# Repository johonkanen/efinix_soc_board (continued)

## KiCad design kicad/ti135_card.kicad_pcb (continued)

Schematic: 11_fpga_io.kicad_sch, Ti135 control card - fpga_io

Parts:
U501: Ti135N484I3; LFBGA-484_18x18mm_Layout22x22_P0.8mm

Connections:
/adasel0_iso: U501.K19 (GPIOT_N_35); also elsewhere on the board
/adasel1_iso: U501.K18 (GPIOT_N_34); also elsewhere on the board
/adasel2_iso: U501.J19 (GPIOT_P_35); also elsewhere on the board
/adbsel0: U501.T19 (GPIOT_P_22_CLK16_P); also elsewhere on the board
/adbsel1: U501.T20 (GPIOT_P_21); also elsewhere on the board
/adbsel2: U501.R19 (GPIOT_N_21); also elsewhere on the board
/adc_cs_n: U501.N1 (GPIOB_P_04_EXTFB); also elsewhere on the board
/adc_sclk: U501.U20 (GPIOT_P_24_CLK18_P); also elsewhere on the board
/adc_sdo: U501.K17 (GPIOT_N_39_CLK15_N); also elsewhere on the board
/adclk_dab: U501.P19 (GPIOT_P_18); also elsewhere on the board
/adclk_iso: U501.J17 (GPIOT_P_34_PLLIN0); also elsewhere on the board
/clk1_iso: U501.L19 (GPIOT_P_37_CDI23_PLLIN0); also elsewhere on the board
/cs1_iso: U501.L17 (GPIOT_N_20); also elsewhere on the board
/dab_pwm_hi_sec: U501.M17 (GPIOT_P_20_PLLIN0); also elsewhere on the board
/dab_pwm_lo_sec: U501.P21 (GPIOT_N_17); also elsewhere on the board
/dab_pwm_pri_hi_iso: U501.N17 (GPIOT_P_02); also elsewhere on the board
/dab_pwm_pri_lo_iso: U501.P20 (GPIOT_P_17); also elsewhere on the board
/emmc_clk: U501.K4 (GPIOB_P_20_EXTSPICLK_CLK6_P); also elsewhere on the board
/emmc_cmd: U501.H2 (GPIOB_N_18_CLK5_N); also elsewhere on the board
/emmc_dat0: U501.F1 (GPIOB_N_22); also elsewhere on the board
/emmc_dat1: U501.F2 (GPIOB_N_24_CDI4); also elsewhere on the board
/emmc_dat2: U501.F3 (GPIOB_P_24_CDI5_EXTFB); also elsewhere on the board
/emmc_dat3: U501.E1 (GPIOB_P_22_EXTFB); also elsewhere on the board
/emmc_dat4: U501.E2 (GPIOB_P_23_CDI7_PLLIN0); also elsewhere on the board
/emmc_dat5: U501.D2 (GPIOB_N_23_CDI6); also elsewhere on the board
/emmc_dat6: U501.B1 (GPIOB_N_21_CLK7_N); also elsewhere on the board
/emmc_dat7: U501.G2 (GPIOB_P_18_CLK5_P); also elsewhere on the board
/emmc_ds: U501.B2 (GPIOB_P_21_CLK7_P); also elsewhere on the board
/emmc_rst_n: U501.A3 (GPIOB_P_28_CSO_CLK11_P); also elsewhere on the board
/eth_int_n: U501.M5 (GPIOB_N_09); also elsewhere on the board
/eth_mdc: U501.M2 (GPIOB_N_06_CDI18); also elsewhere on the board
/eth_mdio: U501.K3 (GPIOB_N_08); also elsewhere on the board
/eth_rst_n: U501.K2 (GPIOB_P_08); also elsewhere on the board
/flash_cs_n: U501.C1 (GPIOB_N_25_SSL_N); also elsewhere on the board
/flash_io0: U501.J4 (GPIOB_N_27_CDI0_CLK10_N); also elsewhere on the board
/flash_io1: U501.J5 (GPIOB_P_27_CDI1_CLK10_P); also elsewhere on the board
/flash_io2: U501.G3 (GPIOB_N_26_CDI2); also elsewhere on the board
/flash_io3: U501.C2 (GPIOB_P_25_CDI3_PLLIN0); also elsewhere on the board
/flash_sck: U501.G4 (GPIOB_P_26_CCK); also elsewhere on the board
/fpga_cbsel0: U501.J1 (GPIOB_N_19_CBSEL0); also elsewhere on the board
/fpga_cbsel1: U501.H1 (GPIOB_P_19_CBSEL1); also elsewhere on the board
/fpga_csi: U501.A2 (GPIOB_N_28_CSI_CLK11_N); also elsewhere on the board
/fpga_ssu_n: U501.L4 (GPIOB_N_20_SSU_N_CLK6_N); also elsewhere on the board
/fpga_test_n: U501.L7 (GPIOB_N_17_TEST_N_CLK4_N); also elsewhere on the board
/gpio_bypass_rly_iso: U501.T21 (GPIOT_N_24_CLK18_N); also elsewhere on the board
/gpio_bypass_rly_isolated: U501.K16 (GPIOT_P_39_CLK15_P); also elsewhere on the board
/inu_adclk: U501.R21 (GPIOT_P_25_CLK19_P); also elsewhere on the board
/j3_oe_n: U501.L5 (GPIOB_P_09); also elsewhere on the board
/lcd_cs_n: U501.L22 (GPIOR_84); also elsewhere on the board
/lcd_dc: U501.H9 (GPIOL_32_PLLIN1); also elsewhere on the board
/lcd_led: U501.H7 (GPIOL_31); also elsewhere on the board
/lcd_miso: U501.H6 (GPIOL_27_CLK25); also elsewhere on the board
/lcd_mosi: U501.L8 (GPIOR_130_PLLIN1); also elsewhere on the board
/lcd_reset_n: U501.L21 (GPIOR_83); also elsewhere on the board
/lcd_sck: U501.H8 (GPIOL_33); also elsewhere on the board
/led0_n: U501.M22 (GPIOR_82)
/led1_n: U501.M8 (GPIOR_127_CLK8)
/mdata_dab: U501.N20 (GPIOR_79); also elsewhere on the board
/mdata_inu: U501.M20 (GPIOR_78_PLLIN1); also elsewhere on the board
/mdata_iso: U501.N21 (GPIOR_80_CLK12); also elsewhere on the board
/pwm_g1_iso: U501.P18 (GPIOT_N_04_CLK31_N); also elsewhere on the board
/pwm_g2_iso: U501.R18 (GPIOT_N_22_CLK16_N); also elsewhere on the board
/pwm_g3_iso: U501.N16 (GPIOT_N_02); also elsewhere on the board
/pwm_g4_iso: U501.M18 (GPIOT_P_19_EXTFB); also elsewhere on the board
/pwm_q5: U501.T16 (GPIOT_P_00_CLK26_P); also elsewhere on the board
/pwm_q6: U501.R22 (GPIOT_N_25_CLK19_N); also elsewhere on the board
/pwm_q7: U501.T17 (GPIOT_P_01_CLK27_P); also elsewhere on the board
/pwm_q8: U501.T22 (GPIOT_N_23_CLK17_N); also elsewhere on the board
/pwm_trans1_iso: U501.M19 (GPIOT_N_19); also elsewhere on the board
/pwm_trans2_iso: U501.L20 (GPIOT_N_37_CDI22); also elsewhere on the board
/pwm_trans3_iso: U501.N18 (GPIOT_N_18); also elsewhere on the board
/pwm_trans4: U501.R17 (GPIOT_P_04_CLK31_P); also elsewhere on the board
/pwm_trans5: U501.U22 (GPIOT_P_23_CLK17_P); also elsewhere on the board
/pwm_trans6: U501.R16 (GPIOT_N_01_CLK27_N); also elsewhere on the board
/refclk_bl0: U501.N7 (GPIOB_P_00_PLLIN0); also elsewhere on the board
/refclk_bl1: U501.R3 (GPIOB_P_03_PLLIN0); also elsewhere on the board
/refclk_bl2: U501.L2 (GPIOB_P_06_CDI19_PLLIN0); also elsewhere on the board
/rgmii_rx_ctl: U501.N2 (GPIOB_N_12_CDI12); also elsewhere on the board
/rgmii_rxc: U501.P5 (GPIOB_P_14_CLK1_P); also elsewhere on the board
/rgmii_rxd0: U501.N3 (GPIOB_P_12_CDI13); also elsewhere on the board
/rgmii_rxd1: U501.R4 (GPIOB_N_14_CLK1_N); also elsewhere on the board
/rgmii_rxd2: U501.N5 (GPIOB_N_11_CDI14); also elsewhere on the board
/rgmii_rxd3: U501.N6 (GPIOB_P_11_CDI15); also elsewhere on the board
/rgmii_tx_ctl: U501.R2 (GPIOB_N_03); also elsewhere on the board
/rgmii_txc: U501.P6 (GPIOB_N_00); also elsewhere on the board
/rgmii_txd0: U501.P1 (GPIOB_N_04); also elsewhere on the board
/rgmii_txd1: U501.P3 (GPIOB_N_05); also elsewhere on the board
/rgmii_txd2: U501.T6 (GPIOB_N_07_CDI16); also elsewhere on the board
/rgmii_txd3: U501.P4 (GPIOB_P_05); also elsewhere on the board
/sdata1_iso: U501.N22 (GPIOR_81_CLK13); also elsewhere on the board
/t_clk: U501.J6 (GPIOR_131_PERST_Q0_N); also elsewhere on the board
/t_cs_n: U501.F5 (GPIOL_34_PLLIN1); also elsewhere on the board
/t_din: U501.H5 (GPIOR_132); also elsewhere on the board
/t_do: U501.F4 (GPIOL_26_CLK24); also elsewhere on the board
/t_irq: U501.K6 (GPIOR_129_PLLIN1); also elsewhere on the board
/uart_rx: U501.K7 (GPIOR_128_CLK9); also elsewhere on the board
/uart_tx: U501.G6 (GPIOL_28); also elsewhere on the board

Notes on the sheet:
U501 Ti135N484I3 I/O banks. Signal <-> ball assignment from efinity/pinplan/pinplan.py (Interface Designer project, design check passed). Change pins there, then re-run this script. HSIO banks (4A, 4B, 2A-2C) are 1.8 V; HVIO banks (BR1_BL3, BR0, TR1) are 3.3 V.

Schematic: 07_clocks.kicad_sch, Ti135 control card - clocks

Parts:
C701: 100n; C_0201_0603Metric; LCSC C190183
R701, R702, R703: 33R; R_0402_1005Metric; LCSC C25105
Y701: OT322525MJBA4SL; Oscillator_SMD_SiT_PQFN-4Pin_3.2x2.5mm; LCSC C669088

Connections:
1V8: C701.1, Y701.1 (EN), Y701.4 (Vdd); also elsewhere on the board
/refclk_bl0: R701.2; also elsewhere on the board
/refclk_bl1: R702.2; also elsewhere on the board
/refclk_bl2: R703.2; also elsewhere on the board
GND: C701.2, Y701.2 (GND); also elsewhere on the board
unnamed: R701.1, R702.1, R703.1, Y701.3 (OUT)

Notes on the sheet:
25 MHz reference: Y701 -> 3 x 33 R (at Y701) -> PLL_BL0/BL1/BL2 reference pins N7/R3/L2 (bank 4B, 1.8 V). Star from the oscillator, one series resistor per branch; keep the branches short and similar in length.
Y701 EN (pin 1) tied to 1V8: always enabled.

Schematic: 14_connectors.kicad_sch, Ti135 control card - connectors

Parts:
J2: UART 3.3V; PinHeader_1x03_P2.54mm_Vertical; LCSC C2937625
J3: 2x19 1.27mm socket (bottom); PinSocket_2x19_P1.27mm_Vertical_Drill0.6; LCSC C27985219
J5: LCD 1x14 2.54mm; PinHeader_1x14_P2.54mm_Vertical; LCSC C22465874
R1401, R1402: 1k; R_0402_1005Metric; LCSC C11702
RN1401, RN1402, RN1403, RN1404, RN1405, RN1406, RN1407, RN1408: 4x10k; R_Array_Convex_4x0402; MPN 4D02WGJ0103TCE; LCSC C25725

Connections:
3V3: J5.14; also elsewhere on the board
/adasel0_iso_3v3: J3.11, RN1402.2 (R2.1); also elsewhere on the board
/adasel1_iso_3v3: J3.10, RN1402.1 (R1.1); also elsewhere on the board
/adasel2_iso_3v3: J3.9, RN1401.4 (R4.1); also elsewhere on the board
/adclk_dab_3v3: J3.24, RN1405.3 (R3.1); also elsewhere on the board
/adclk_iso_3v3: J3.7, RN1401.2 (R2.1); also elsewhere on the board
/clk1_iso_3v3: J3.14, RN1403.1 (R1.1); also elsewhere on the board
/cs1_iso_3v3: J3.13, RN1402.4 (R4.1); also elsewhere on the board
/dab_pwm_hi_sec_3v3: J3.27, RN1406.2 (R2.1); also elsewhere on the board
/dab_pwm_lo_sec_3v3: J3.29, RN1406.4 (R4.1); also elsewhere on the board
/dab_pwm_pri_hi_iso_3v3: J3.22, RN1405.1 (R1.1); also elsewhere on the board
/dab_pwm_pri_lo_iso_3v3: J3.23, RN1405.2 (R2.1); also elsewhere on the board
/gpio_bypass_rly_iso_3v3: J3.36, RN1408.3 (R3.1); also elsewhere on the board
/gpio_bypass_rly_isolated_3v3: J3.8, RN1401.3 (R3.1); also elsewhere on the board
/inu_adclk_3v3: J3.32, RN1407.3 (R3.1); also elsewhere on the board
/isoada1: J3.4; also elsewhere on the board
/isoada2: J3.3; also elsewhere on the board
/isoada3: J3.1; also elsewhere on the board
/lcd_cs_n: J5.12; also elsewhere on the board
/lcd_dc: J5.10; also elsewhere on the board
/lcd_led: J5.7; also elsewhere on the board
/lcd_miso: J5.6; also elsewhere on the board
/lcd_mosi: J5.9; also elsewhere on the board
/lcd_reset_n: J5.11; also elsewhere on the board
/lcd_sck: J5.8; also elsewhere on the board
/mdata_dab: J3.26, RN1406.1 (R1.1); also elsewhere on the board
/mdata_inu: J3.34, RN1408.1 (R1.1); also elsewhere on the board
/mdata_iso: J3.6, RN1401.1 (R1.1); also elsewhere on the board
/pwm_g1_iso_3v3: J3.20, RN1404.3 (R3.1); also elsewhere on the board
/pwm_g2_iso_3v3: J3.19, RN1404.2 (R2.1); also elsewhere on the board
/pwm_g3_iso_3v3: J3.21, RN1404.4 (R4.1); also elsewhere on the board
/pwm_g4_iso_3v3: J3.18, RN1404.1 (R1.1); also elsewhere on the board
/pwm_q5_3v3: J3.30, RN1407.1 (R1.1); also elsewhere on the board
/pwm_q6_3v3: J3.31, RN1407.2 (R2.1); also elsewhere on the board
/pwm_q7_3v3: J3.37, RN1408.4 (R4.1); also elsewhere on the board
/pwm_q8_3v3: J3.33, RN1407.4 (R4.1); also elsewhere on the board
/pwm_trans1_iso_3v3: J3.15, RN1403.2 (R2.1); also elsewhere on the board
/pwm_trans2_iso_3v3: J3.16, RN1403.3 (R3.1); also elsewhere on the board
/pwm_trans3_iso_3v3: J3.17, RN1403.4 (R4.1); also elsewhere on the board
/pwm_trans4_3v3: J3.25, RN1405.4 (R4.1); also elsewhere on the board
/pwm_trans5_3v3: J3.35, RN1408.2 (R2.1); also elsewhere on the board
/pwm_trans6_3v3: J3.28, RN1406.3 (R3.1); also elsewhere on the board
/res1: J3.38; also elsewhere on the board
/sdata1_iso: J3.12, RN1402.3 (R3.1); also elsewhere on the board
/t_clk: J5.5; also elsewhere on the board
/t_cs_n: J5.4; also elsewhere on the board
/t_din: J5.3; also elsewhere on the board
/t_do: J5.2; also elsewhere on the board
/t_irq: J5.1; also elsewhere on the board
/uart_rx: R1401.1; also elsewhere on the board
/uart_tx: R1402.1; also elsewhere on the board
GND: J2.3, J3.2, J3.5, J5.13, RN1401.5 (R4.2), RN1401.6 (R3.2), RN1401.7 (R2.2), RN1401.8 (R1.2), RN1402.5 (R4.2), RN1402.6 (R3.2), RN1402.7 (R2.2), RN1402.8 (R1.2), RN1403.5 (R4.2), RN1403.6 (R3.2), RN1403.7 (R2.2), RN1403.8 (R1.2), RN1404.5 (R4.2), RN1404.6 (R3.2), RN1404.7 (R2.2), RN1404.8 (R1.2), RN1405.5 (R4.2), RN1405.6 (R3.2), RN1405.7 (R2.2), RN1405.8 (R1.2), RN1406.5 (R4.2), RN1406.6 (R3.2), RN1406.7 (R2.2), RN1406.8 (R1.2), RN1407.5 (R4.2), RN1407.6 (R3.2), RN1407.7 (R2.2), RN1407.8 (R1.2), RN1408.5 (R4.2), RN1408.6 (R3.2), RN1408.7 (R2.2), RN1408.8 (R1.2); also elsewhere on the board
unnamed: J2.1, R1401.2
unnamed: J2.2, R1402.2

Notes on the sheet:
J5: LCD/touch header, Ti60 J4 pinout (wired to the LCD with jumper wires).
J3 = baseboard J11 (2x19 1.27 mm socket on B.Cu, pin n = baseboard pin n, see MECHANICAL.md). Every signal pin has a 10 k pull-down so the power board sees low while the FPGA is unconfigured and the translators are disabled (MIGRATION_PLAN.md 3.2).
J2: FPGA UART, Ti60 J8 pinout.
lcd_mosi / lcd_miso exchanged at J5 2026-11-17

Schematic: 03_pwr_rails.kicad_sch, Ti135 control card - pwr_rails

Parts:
C301, C311, C331, C341: 10u; C_0603_1608Metric; LCSC C109457
C302, C312, C332, C342: 22u; C_0603_1608Metric; LCSC C109447
C303, C313, C335, C343: 100n; C_0201_0603Metric; LCSC C190183
C304, C314, C333, C344: 47u; C_0805_2012Metric; LCSC C16780
C305, C315, C334, C345: 33p; C_0201_0603Metric; LCSC C277477
L301, L311, L331, L341: 1u; L_2520_FTC252012S; MPN FTC252012S1R0MBCA; LCSC C5832370
R301, R311, R331, R341: 200k; R_0201_0603Metric; LCSC C138163
R302: 100k; R_0201_0603Metric; LCSC C106224
R312: 44.2k; R_0201_0603Metric; LCSC C226551
R332: 475k; R_0201_0603Metric; LCSC C388079
R342: 243k; R_0201_0603Metric; LCSC C423644
U301, U311: AP61202Z6-7; SOT-563; LCSC C5188956
U331, U341: AP61203Z6-7; SOT-563; LCSC C5244557

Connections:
0V85: C332.1, C333.1, C334.1, L331.2, R331.1; also elsewhere on the board
1V1: C342.1, C344.1, C345.1, L341.2, R341.1; also elsewhere on the board
1V8: C302.1, C304.1, C305.1, L301.2, R301.1; also elsewhere on the board
3V3: C312.1, C314.1, C315.1, L311.2, R311.1; also elsewhere on the board
5V0: C301.1, C303.1, C311.1, C313.1, C331.1, C335.1, C341.1, C343.1, U301.3 (VIN), U301.5 (EN), U311.3 (VIN), U311.5 (EN), U331.3 (VIN), U341.3 (VIN); also elsewhere on the board
/pg_group1: U301.6 (PG), U311.6 (PG), U331.5 (EN), U341.5 (EN); also elsewhere on the board
GND: C301.2, C302.2, C303.2, C304.2, C311.2, C312.2, C313.2, C314.2, C331.2, C332.2, C333.2, C335.2, C341.2, C342.2, C343.2, C344.2, R302.2, R312.2, R332.2, R342.2, U301.2 (GND), U311.2 (GND), U331.2 (GND), U341.2 (GND); also elsewhere on the board
unnamed: C305.2, R301.2, R302.1, U301.1 (FB)
unnamed: L301.1, U301.4 (SW)
unnamed: C315.2, R311.2, R312.1, U311.1 (FB)
unnamed: L311.1, U311.4 (SW)
unnamed: C334.2, R331.2, R332.1, U331.1 (FB)
unnamed: L331.1, U331.4 (SW)
unnamed: C345.2, R341.2, R342.1, U341.1 (FB)
unnamed: L341.1, U341.4 (SW)

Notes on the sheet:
1V1 DDR I/O + LPDDR4 VDD2/VDDQ (group 2)
1V8 (group 1)
0V85 DDR PHY (group 2)
3V3 (group 1)
Group 1: 1V8 (VCCAUX, HSIO, LPDDR4 VDD1, eMMC VCCQ, flash), 3V3 (HVIO, eMMC VCC, PHY, translators). Group 2 (EN = pg_group1): 0V85 (DDR PHY VDD_PHY / VDDPLL), 1V1 (DDR VDDQ/VDDQX/VDDQ_CK, LPDDR4 VDD2/VDDQ).

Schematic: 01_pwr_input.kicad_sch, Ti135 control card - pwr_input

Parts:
C101: 47u; C_1206_3216Metric; LCSC C96123
C102: 22u; C_0805_2012Metric; LCSC C45783
C103: 100n; C_0402_1005Metric; LCSC C1525
C104, C105: 1u; C_0402_1005Metric; LCSC C52923
J6: 2x3 1.27mm (bottom); PinSocket_2x03_P1.27mm_Vertical; LCSC C22373841
J101: 5V0 bench input; PinHeader_1x02_P2.54mm_Vertical; LCSC C492401
U101: NCP163ASN330T1G; SOT-23-5; LCSC C603656

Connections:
3V3_analog: C105.1, U101.5 (VOUT); also elsewhere on the board
5V0: C101.1, C102.1, C103.1, C104.1, J6.2, J6.4, J6.6, J101.1, U101.1 (VIN), U101.3 (EN); also elsewhere on the board
GND: C101.2, C102.2, C103.2, C104.2, C105.2, J6.1, J6.3, J6.5, J101.2, U101.2 (GND); also elsewhere on the board

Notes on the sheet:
J101: 2.54 mm 1x2 header near J6 to power the card from a bench supply with female jumpers, without the baseboard (pin 1 = 5V0, pin 2 = GND). Do not feed it while the baseboard powers J6.
3V3_analog: LDO for the ADC block (sheet 13).
J6 = baseboard J12 (2x3 1.27 mm on B.Cu, MECHANICAL.md): 5V0 = baseboard 5V_ISOL, GND = ISOGND. Supply budget and limits: POWER_BUDGET.md (baseboard U8 to be upgraded to 1.5-2 A).
Input bulk (the regulators also have their own 10u).

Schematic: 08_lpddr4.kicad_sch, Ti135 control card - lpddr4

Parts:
C803: 22u; C_0402_1005Metric; LCSC C415703
C804, C805, C810, C811, C812, C813, C814, C815, C816, C817, C818, C819, C820, C821, C822, C827, C828, C829, C830, C831, C832, C833, C834, C835, C836, C837, C838, C839, C840: 100n; C_0201_0603Metric; LCSC C190183
C806, C807, C823, C824: 22u; C_0402_1005Metric; LCSC C415703; not fitted
C808, C809, C825, C826: 1u; C_0201_0603Metric; LCSC C272877
R801: 240R 0.5%; R_0201_0603Metric; MPN RC0201DR-07240RL; LCSC C851687
R802: 240R 1%; R_0402_1005Metric; LCSC C25094
R803: 15R; R_0402_1005Metric; LCSC C25083
R804: 10k 1%; R_0201_0603Metric; LCSC C106225
U501: Ti135N484I3; LFBGA-484_18x18mm_Layout22x22_P0.8mm
U801: H9HCNNN8KUMLHR-NMO; BGA-200_10x15mm_Layout12x22_P0.8x0.65mm; LCSC C51891855

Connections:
1V1: C806.1, C807.1, C808.1, C809.1, C810.1, C811.1, C812.1, C813.1, C814.1, C815.1, C816.1, C817.1, C818.1, C819.1, C820.1, C821.1, C822.1, C823.1, C824.1, C825.1, C826.1, C827.1, C828.1, C829.1, C830.1, C831.1, C832.1, C833.1, C834.1, C835.1, C836.1, C837.1, C838.1, C839.1, C840.1, R802.2, U801.A4 (VDD2), U801.A9 (VDD2), U801.AA3 (VDDQ), U801.AA5 (VDDQ), U801.AA8 (VDDQ), U801.AA10 (VDDQ), U801.AB4 (VDD2), U801.AB9 (VDD2), U801.B3 (VDDQ), U801.B5 (VDDQ), U801.B8 (VDDQ), U801.B10 (VDDQ), U801.D1 (VDDQ), U801.D5 (VDDQ), U801.D8 (VDDQ), U801.D12 (VDDQ), U801.F3 (VDDQ), U801.F5 (VDD2), U801.F8 (VDD2), U801.F10 (VDDQ), U801.G2 (ODT_CA_A), U801.H1 (VDD2), U801.H5 (VDD2), U801.H8 (VDD2), U801.H12 (VDD2), U801.K1 (VDD2), U801.K3 (VDD2), U801.K10 (VDD2), U801.K12 (VDD2), U801.N1 (VDD2), U801.N3 (VDD2), U801.N10 (VDD2), U801.N12 (VDD2), U801.R1 (VDD2), U801.R5 (VDD2), U801.R8 (VDD2), U801.R12 (VDD2), U801.T2 (ODT_CA_B), U801.U3 (VDDQ), U801.U5 (VDD2), U801.U8 (VDD2), U801.U10 (VDDQ), U801.W1 (VDDQ), U801.W5 (VDDQ), U801.W8 (VDDQ), U801.W12 (VDDQ); also elsewhere on the board
1V8: C803.1, C804.1, C805.1, U801.F1 (VDD1), U801.F12 (VDD1), U801.G4 (VDD1), U801.G9 (VDD1), U801.T4 (VDD1), U801.T9 (VDD1), U801.U1 (VDD1), U801.U12 (VDD1); also elsewhere on the board
/08 lpddr4/ddr_ca0: U501.AB15 (DDR_A[0]), U801.H2 (CA0_A), U801.R2 (CA0_B)
/08 lpddr4/ddr_ca1: U501.AA15 (DDR_A[1]), U801.J2 (CA1_A), U801.P2 (CA1_B)
/08 lpddr4/ddr_ca2: U501.AA14 (DDR_A[2]), U801.H9 (CA2_A), U801.R9 (CA2_B)
/08 lpddr4/ddr_ca3: U501.Y14 (DDR_A[3]), U801.H10 (CA3_A), U801.R10 (CA3_B)
/08 lpddr4/ddr_ca4: U501.W14 (DDR_A[4]), U801.H11 (CA4_A), U801.R11 (CA4_B)
/08 lpddr4/ddr_ca5: U501.W13 (DDR_A[5]), U801.J11 (CA5_A), U801.P11 (CA5_B)
/08 lpddr4/ddr_ck_N: U501.AA13 (DDR_CK_N), U801.J9 (CK_C_A), U801.P9 (CK_C_B)
/08 lpddr4/ddr_ck_P: U501.AB13 (DDR_CK), U801.J8 (CK_T_A), U801.P8 (CK_T_B)
/08 lpddr4/ddr_cke0: R803.2, U801.J4 (CKE0_A), U801.P4 (CKE0_B)
/08 lpddr4/ddr_cke0_fpga: R803.1, U501.AB11 (DDR_CKE[0])
/08 lpddr4/ddr_cs0_n: U501.AB9 (DDR_CS_N[0]), U801.H4 (CS0_A)
/08 lpddr4/ddr_cs2_n: U501.AA8 (DDR_CS_N[2]), U801.R4 (CS0_B)
/08 lpddr4/ddr_dm0: U501.W3 (DDR_DM[0]), U801.C3 (DMI0_A)
/08 lpddr4/ddr_dm1: U501.AA3 (DDR_DM[1]), U801.C10 (DMI1_A)
/08 lpddr4/ddr_dm2: U501.W18 (DDR_DM[2]), U801.Y3 (DMI0_B)
/08 lpddr4/ddr_dm3: U501.Y20 (DDR_DM[3]), U801.Y10 (DMI1_B)
/08 lpddr4/ddr_dq0: U501.U2 (DDR_DQ[1]), U801.B2 (DQ0_A)
/08 lpddr4/ddr_dq1: U501.AB2 (DDR_DQ[6]), U801.C2 (DQ1_A)
/08 lpddr4/ddr_dq2: U501.V3 (DDR_DQ[3]), U801.E2 (DQ2_A)
/08 lpddr4/ddr_dq3: U501.U3 (DDR_DQ[0]), U801.F2 (DQ3_A)
/08 lpddr4/ddr_dq4: U501.Y2 (DDR_DQ[4]), U801.F4 (DQ4_A)
/08 lpddr4/ddr_dq5: U501.AA2 (DDR_DQ[7]), U801.E4 (DQ5_A)
/08 lpddr4/ddr_dq6: U501.AA1 (DDR_DQ[5]), U801.C4 (DQ6_A)
/08 lpddr4/ddr_dq7: U501.U1 (DDR_DQ[2]), U801.B4 (DQ7_A)
/08 lpddr4/ddr_dq8: U501.W4 (DDR_DQ[11]), U801.B11 (DQ8_A)
/08 lpddr4/ddr_dq9: U501.V5 (DDR_DQ[9]), U801.C11 (DQ9_A)
/08 lpddr4/ddr_dq10: U501.AB5 (DDR_DQ[13]), U801.E11 (DQ10_A)
/08 lpddr4/ddr_dq11: U501.AA6 (DDR_DQ[14]), U801.F11 (DQ11_A)
/08 lpddr4/ddr_dq12: U501.AB7 (DDR_DQ[15]), U801.F9 (DQ12_A)
/08 lpddr4/ddr_dq13: U501.W5 (DDR_DQ[10]), U801.E9 (DQ13_A)
/08 lpddr4/ddr_dq14: U501.AA5 (DDR_DQ[12]), U801.C9 (DQ14_A)
/08 lpddr4/ddr_dq15: U501.U4 (DDR_DQ[8]), U801.B9 (DQ15_A)
/08 lpddr4/ddr_dq16: U501.V18 (DDR_DQ[20]), U801.AA2 (DQ0_B)
/08 lpddr4/ddr_dq17: U501.AB17 (DDR_DQ[19]), U801.Y2 (DQ1_B)
/08 lpddr4/ddr_dq18: U501.Y16 (DDR_DQ[17]), U801.V2 (DQ2_B)
/08 lpddr4/ddr_dq19: U501.W16 (DDR_DQ[23]), U801.U2 (DQ3_B)
/08 lpddr4/ddr_dq20: U501.AA16 (DDR_DQ[16]), U801.U4 (DQ4_B)
/08 lpddr4/ddr_dq21: U501.V16 (DDR_DQ[22]), U801.V4 (DQ5_B)
/08 lpddr4/ddr_dq22: U501.AA17 (DDR_DQ[18]), U801.Y4 (DQ6_B)
/08 lpddr4/ddr_dq23: U501.V17 (DDR_DQ[21]), U801.AA4 (DQ7_B)
/08 lpddr4/ddr_dq24: U501.W21 (DDR_DQ[29]), U801.AA11 (DQ8_B)
/08 lpddr4/ddr_dq25: U501.AA20 (DDR_DQ[26]), U801.Y11 (DQ9_B)
/08 lpddr4/ddr_dq26: U501.AA19 (DDR_DQ[27]), U801.V11 (DQ10_B)
/08 lpddr4/ddr_dq27: U501.W19 (DDR_DQ[30]), U801.U11 (DQ11_B)
/08 lpddr4/ddr_dq28: U501.W20 (DDR_DQ[31]), U801.U9 (DQ12_B)
/08 lpddr4/ddr_dq29: U501.AB19 (DDR_DQ[24]), U801.V9 (DQ13_B)
/08 lpddr4/ddr_dq30: U501.AB21 (DDR_DQ[25]), U801.Y9 (DQ14_B)
/08 lpddr4/ddr_dq31: U501.W22 (DDR_DQ[28]), U801.AA9 (DQ15_B)
/08 lpddr4/ddr_dqs0_N: U501.W1 (DDR_DQS_N[0]), U801.E3 (DQS0_C_A)
/08 lpddr4/ddr_dqs0_P: U501.W2 (DDR_DQS[0]), U801.D3 (DQS0_T_A)
/08 lpddr4/ddr_dqs1_N: U501.AA4 (DDR_DQS_N[1]), U801.E10 (DQS1_C_A)
/08 lpddr4/ddr_dqs1_P: U501.Y4 (DDR_DQS[1]), U801.D10 (DQS1_T_A)
/08 lpddr4/ddr_dqs2_N: U501.AA18 (DDR_DQS_N[2]), U801.V3 (DQS0_C_B)
/08 lpddr4/ddr_dqs2_P: U501.Y18 (DDR_DQS[2]), U801.W3 (DQS0_T_B)
/08 lpddr4/ddr_dqs3_N: U501.AA22 (DDR_DQS_N[3]), U801.V10 (DQS1_C_B)
/08 lpddr4/ddr_dqs3_P: U501.AA21 (DDR_DQS[3]), U801.W10 (DQS1_T_B)
/08 lpddr4/ddr_rst_n: R804.1, U501.AA12 (DDR_RST_N), U801.T11 (RESET_N)
GND: C803.2, C804.2, C805.2, C806.2, C807.2, C808.2, C809.2, C810.2, C811.2, C812.2, C813.2, C814.2, C815.2, C816.2, C817.2, C818.2, C819.2, C820.2, C821.2, C822.2, C823.2, C824.2, C825.2, C826.2, C827.2, C828.2, C829.2, C830.2, C831.2, C832.2, C833.2, C834.2, C835.2, C836.2, C837.2, C838.2, C839.2, C840.2, R801.2, R804.2, U801.A3 (VSS), U801.A10 (VSS), U801.AB3 (VSS), U801.AB5 (VSS), U801.AB8 (VSS), U801.AB10 (VSS), U801.C1 (VSS), U801.C5 (VSS), U801.C8 (VSS), U801.C12 (VSS), U801.D2 (VSS), U801.D4 (VSS), U801.D9 (VSS), U801.D11 (VSS), U801.E1 (VSS), U801.E5 (VSS), U801.E8 (VSS), U801.E12 (VSS), U801.G1 (VSS), U801.G3 (VSS), U801.G5 (VSS), U801.G8 (VSS), U801.G10 (VSS), U801.G12 (VSS), U801.J1 (VSS), U801.J3 (VSS), U801.J10 (VSS), U801.J12 (VSS), U801.K2 (VSS), U801.K4 (VSS), U801.K9 (VSS), U801.K11 (VSS), U801.N2 (VSS), U801.N4 (VSS), U801.N9 (VSS), U801.N11 (VSS), U801.P1 (VSS), U801.P3 (VSS), U801.P10 (VSS), U801.P12 (VSS), U801.T1 (VSS), U801.T3 (VSS), U801.T5 (VSS), U801.T8 (VSS), U801.T10 (VSS), U801.T12 (VSS), U801.V1 (VSS), U801.V5 (VSS), U801.V8 (VSS), U801.V12 (VSS), U801.W2 (VSS), U801.W4 (VSS), U801.W9 (VSS), U801.W11 (VSS), U801.Y1 (VSS), U801.Y5 (VSS), U801.Y8 (VSS), U801.Y12 (VSS); also elsewhere on the board
unnamed: R801.1, U501.Y9 (DDR_CAL)
unnamed: R802.1, U801.A5 (ZQ0)

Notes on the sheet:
LPDDR4 x32: U501 DDR block -> U801 (2 channels x16, single rank). Wiring per TI135_PCB_NOTES.md §6.1 (Efinix Ti375C529 kit). DQ swizzled within each byte (LPDDR4_SWIZZLE.md, efinity/pinplan/lpddr4_swizzle.json, Interface Designer PIN_SWIZZLE_DQM0-3). Never DM/DQS/bytes/channels; CA not swizzled. Ro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
U801 VDD1 (1V8): 22u + 2 x 100n
U801 VDD2 (1V1): 2 x 22u + 2 x 1u + 13 x 100n
CKE series 15R on B.Cu at the U501 CKE via (sim/lpddr4_si/results/routed_corners.md): CKE has no ODT; without it the max-corner peak at 3200 Mbps is 1486 mV (limit 1470). Efinity has no CA/CKE drive setting.
U801 VDDQ (1V1): 2 x 22u + 2 x 1u + 14 x 100n (the 100n under the DRAM, the 22u/1u bulk west of it)

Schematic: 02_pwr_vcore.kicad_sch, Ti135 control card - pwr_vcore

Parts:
C201: 10u; C_0603_1608Metric; LCSC C109457
C202: 22u; C_0603_1608Metric; LCSC C109447
C203: 100n; C_0201_0603Metric; LCSC C190183
C204: 47u; C_0805_2012Metric; LCSC C16780
C205: 33p; C_0201_0603Metric; LCSC C277477
L201: 1u; L_2520_FTC252012S; MPN FTC252012S1R0MBCA; LCSC C5832370
R201: 200k; R_0201_0603Metric; LCSC C138163
R202: 340k; R_0201_0603Metric; LCSC C423573
U201: AP61203Z6-7; SOT-563; LCSC C5244557

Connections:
5V0: C201.1, C203.1, U201.3 (VIN), U201.5 (EN); also elsewhere on the board
/pg_group1: U201.6 (PG); also elsewhere on the board
GND: C201.2, C202.2, C203.2, C204.2, R202.2, U201.2 (GND); also elsewhere on the board
unnamed: C205.2, R201.2, R202.1, U201.1 (FB)
unnamed: L201.1, U201.4 (SW)
VCORE: C202.1, C204.1, C205.1, L201.2, R201.1; also elsewhere on the board

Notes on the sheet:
VCORE 0.95 V: Ti135 VCC (31 balls), VCCA_BL/BR/TR (through ferrites, sheet 5), VDD_SOC, VCC18A_MIPI (unused MIPI). Estimate about 0.6 A typical, 1.0 A high, >= 1.5 A inrush (POWER_BUDGET.md).
VCORE 0.95 V (group 1)

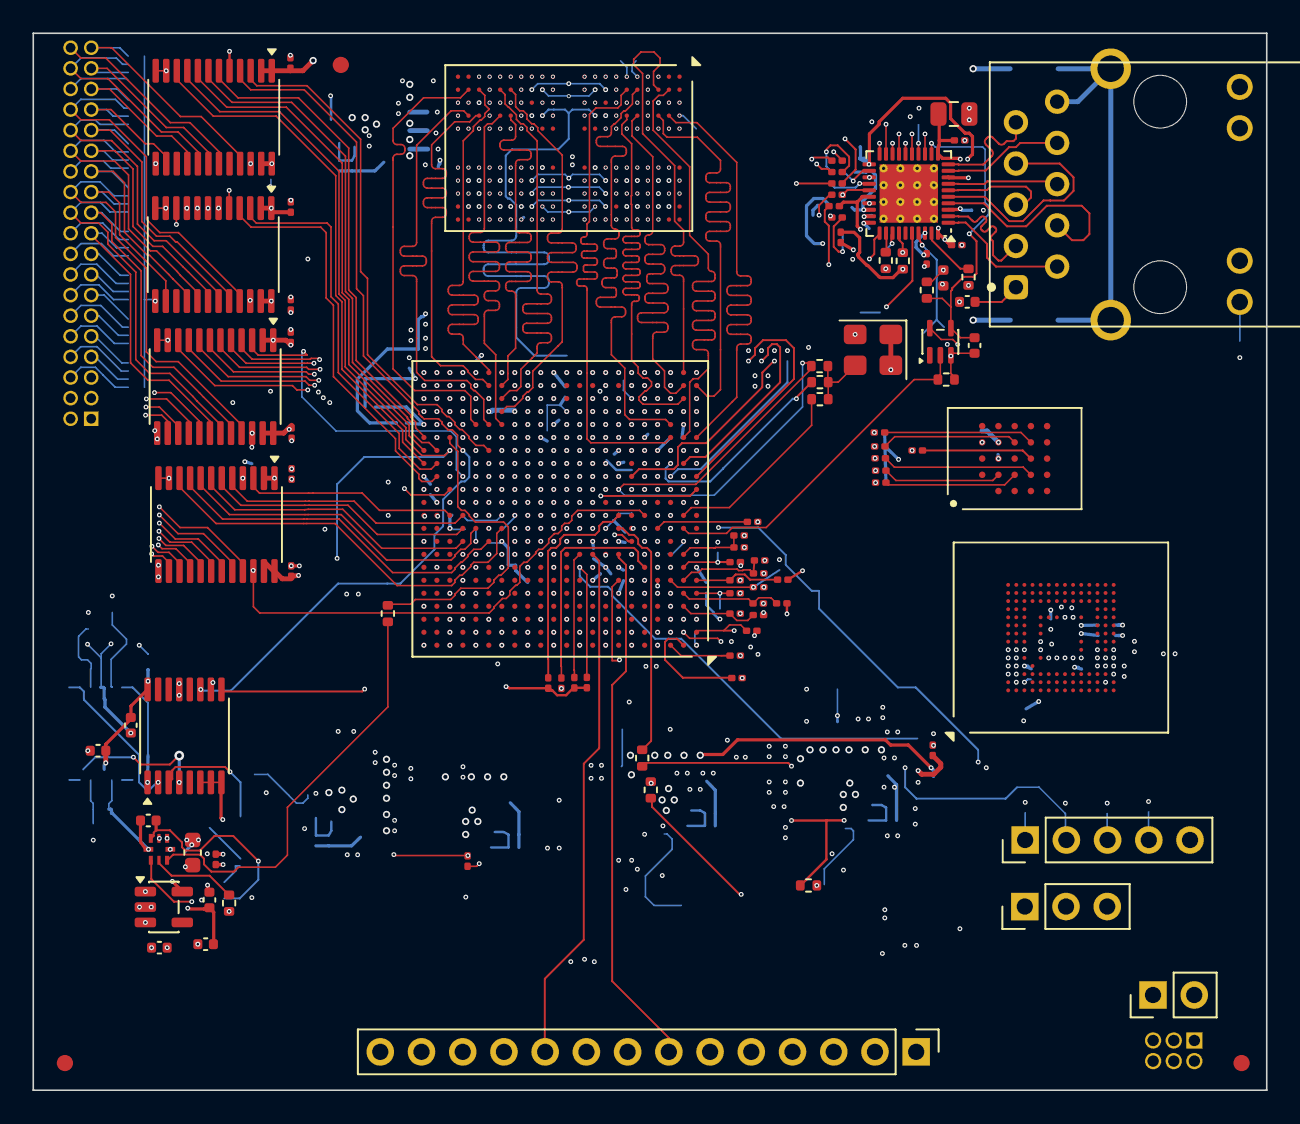
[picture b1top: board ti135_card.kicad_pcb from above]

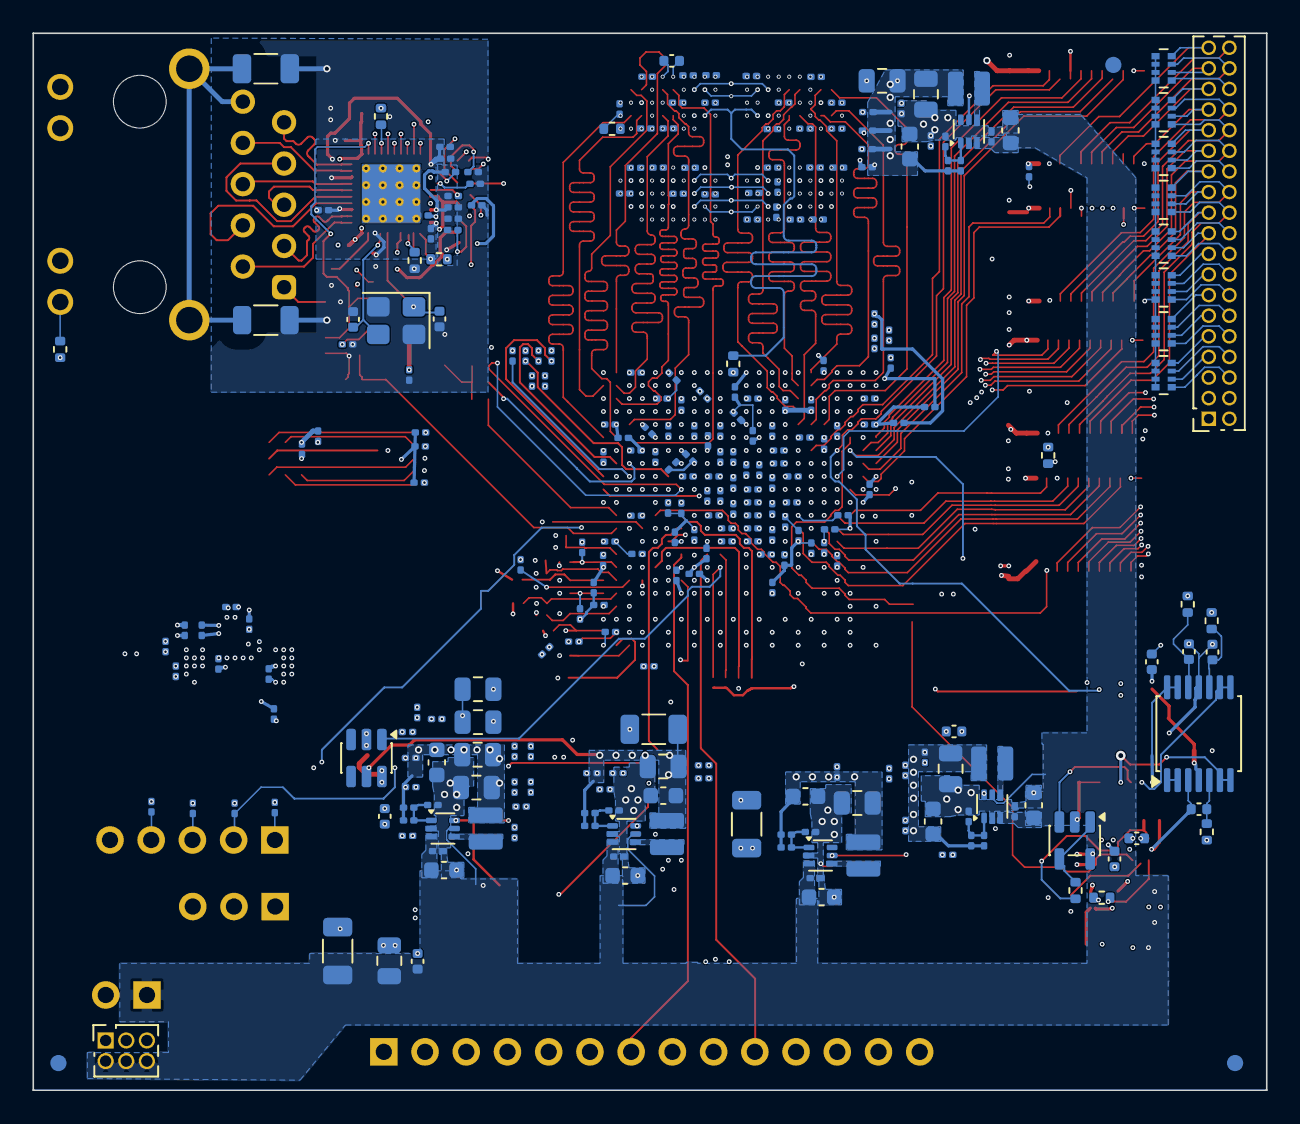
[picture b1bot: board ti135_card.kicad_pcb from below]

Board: 8 copper layers, 76.0 x 65.1 mm, 380 parts (287 on the bottom side), 288 nets.

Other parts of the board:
FID1, FID2, FID3, FID4, FID5, FID6: Fiducial; Fiducial_1mm_Mask2mm
